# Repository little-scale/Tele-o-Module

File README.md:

# Tele-o-Module
Eurorack Module for WiFi / BlueTooth / BLE to 4 CV and 2 Gates

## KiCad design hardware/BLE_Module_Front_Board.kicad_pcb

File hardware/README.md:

Hardware files for Tele-o Module

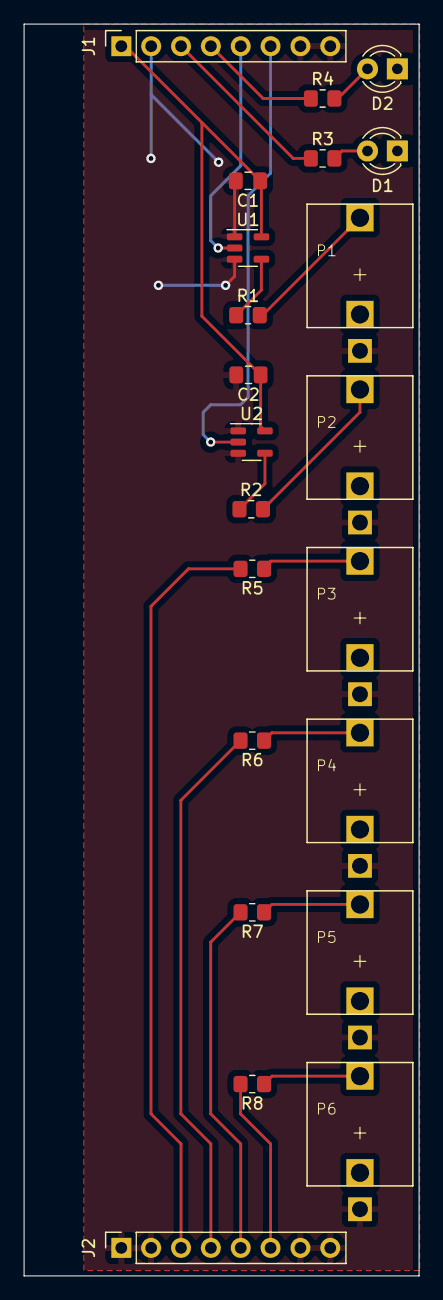
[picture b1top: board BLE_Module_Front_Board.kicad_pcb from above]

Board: 2 copper layers, 33.6 x 106.5 mm, 22 parts (0 on the bottom side), 20 nets.

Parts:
C1, C2: C; C_0805_2012Metric_Pad1.18x1.45mm_HandSolder
D1, D2: LED; LED_D3.0mm
J1, J2: Conn_01x08_Male; PinSocket_1x08_P2.54mm_Vertical
P1, P2, P3, P4, P5, P6: EuroCon; THONKICONN
R1, R2, R3, R4: 1k; R_0805_2012Metric_Pad1.20x1.40mm_HandSolder
R5, R6, R7, R8: 1K; R_0805_2012Metric_Pad1.20x1.40mm_HandSolder
U1, U2: 74AHCT1G125; SOT-23-5

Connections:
+5V: C1.1, C2.1, J1.1, U1.5 (VCC), U2.5 (VCC)
/CV1: J2.3, R5.2
/CV2: J2.4, R6.2
/CV3: J2.5, R7.2
/CV4: J2.6, R8.2
/GATE1: J1.5, U1.2
/GATE2: J1.6, U2.2
/LED1: J1.3, R3.1
/LED2: J1.4, R4.1
GND: C1.2, C2.2, D1.1 (K), D2.1 (K), J1.2, J1.7, J1.8, J2.1, J2.2, J2.7, J2.8, P1.P$1_SLEEVE, P2.P$1_SLEEVE, P3.P$1_SLEEVE, P4.P$1_SLEEVE, P5.P$1_SLEEVE, P6.P$1_SLEEVE, U1.1, U1.3 (GND), U2.1, U2.3 (GND)
unnamed: D1.2 (A), R3.2
unnamed: D2.2 (A), R4.2
unnamed: P1.P$3_TIP, R1.2
unnamed: P2.P$3_TIP, R2.2
unnamed: P3.P$3_TIP, R5.1
unnamed: P4.P$3_TIP, R6.1
unnamed: P5.P$3_TIP, R7.1
unnamed: P6.P$3_TIP, R8.1
unnamed: R1.1, U1.4
unnamed: R2.1, U2.4

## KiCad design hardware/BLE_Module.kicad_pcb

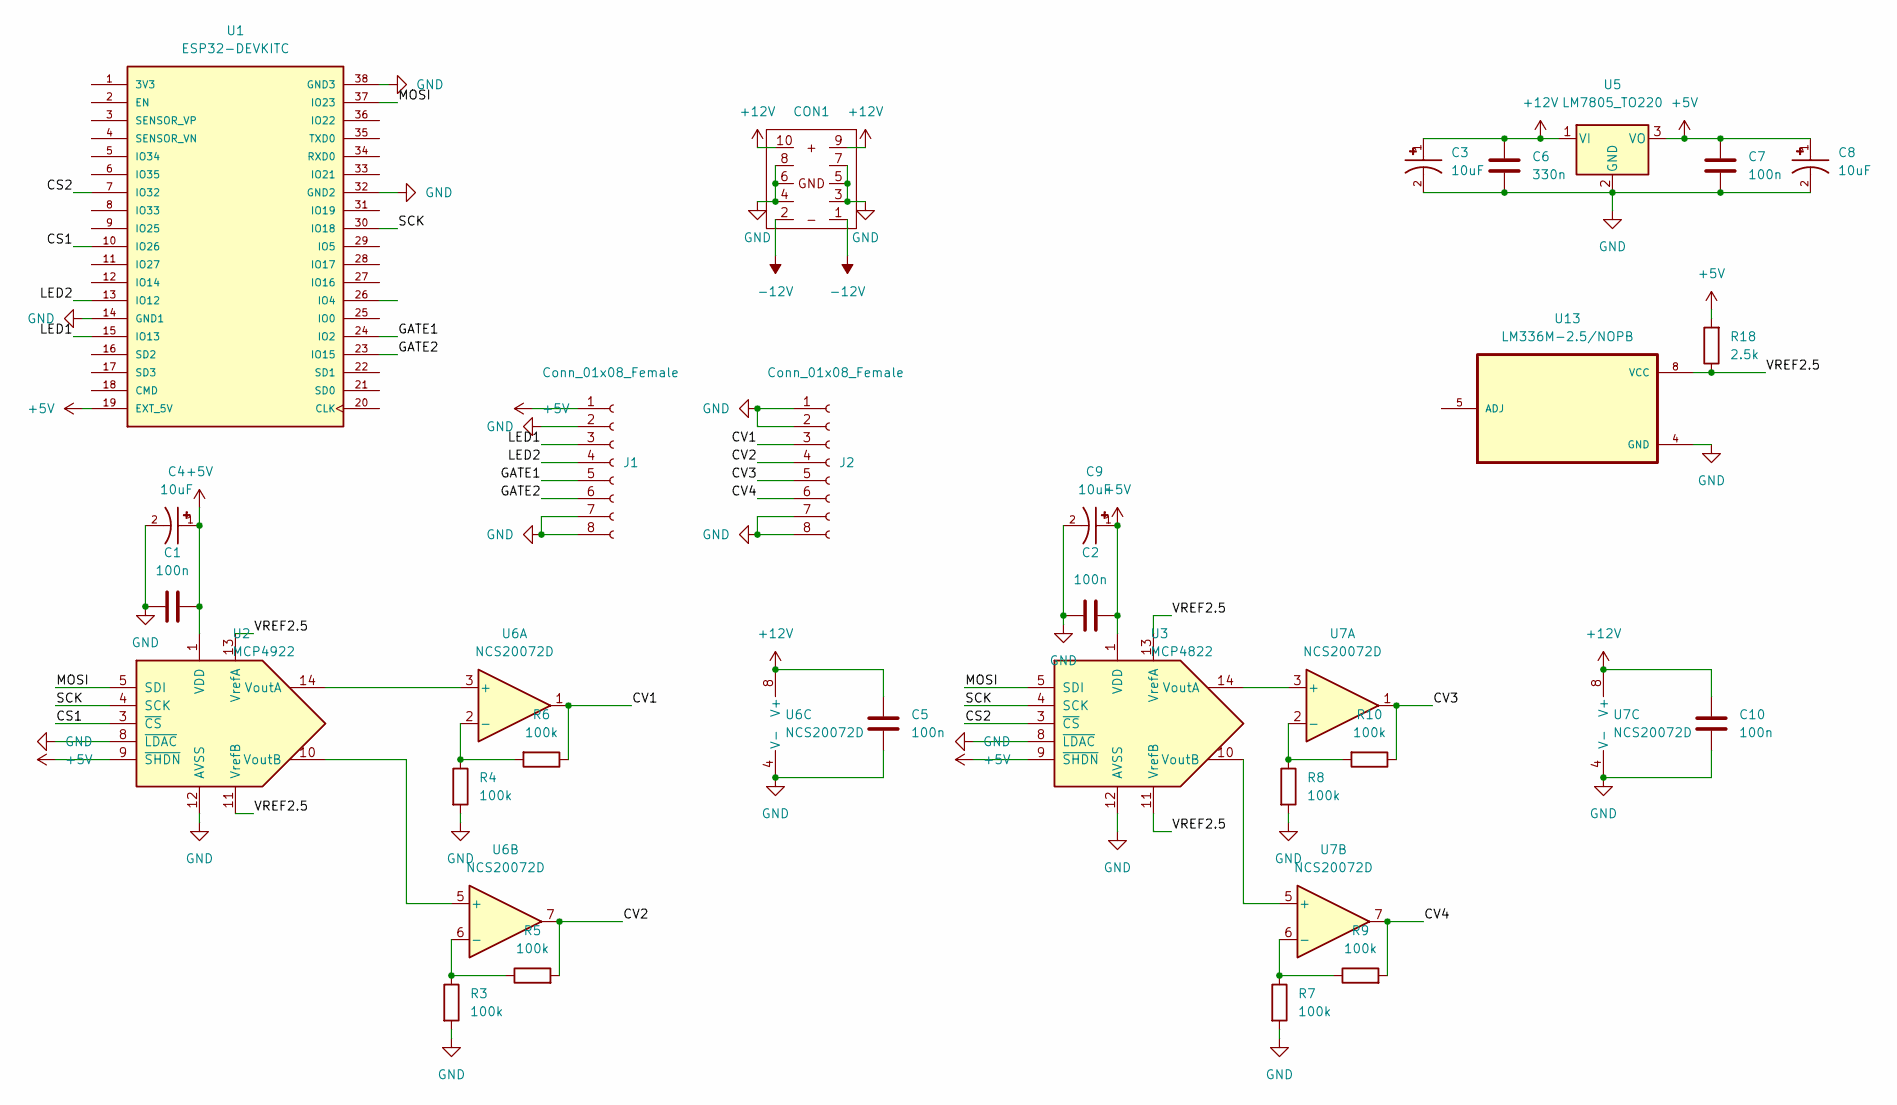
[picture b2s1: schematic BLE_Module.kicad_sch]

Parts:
C1, C2, C5, C7, C10: 100n; C_0805_2012Metric_Pad1.18x1.45mm_HandSolder
C3, C4, C8, C9: 10uF; CAP_EEEFN1E100R; PARTREV 10-Oct-19
C6: 330n; C_0805_2012Metric_Pad1.18x1.45mm_HandSolder
CON1: EuroPow; EURO_POWER_HEADER
J1, J2: Conn_01x08_Female; PinSocket_1x08_P2.54mm_Vertical
R3, R4, R5, R6, R7, R8, R9, R10: 100k; R_0805_2012Metric_Pad1.20x1.40mm_HandSolder
R18: 2.5k; R_0805_2012Metric_Pad1.20x1.40mm_HandSolder
U1: ESP32-DEVKITC; MODULE_ESP32-DEVKITC; PARTREV N/A
U2: MCP4922; SOIC127P600X175-14N
U3: MCP4822; SOIC127P600X175-14N
U5: LM7805_TO220; TO-220-3_Vertical
U6, U7: NCS20072D; SOIC-8_3.9x4.9mm_P1.27mm
U13: LM336M-2.5/NOPB; SOIC127P599X175-8N

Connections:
+5V: C1.2, C2.2, C4.1, C7.1, C8.1, C9.1, J1.1, R18.2, U1.19 (EXT_5V), U2.1 (VDD), U2.9 (~SHDN), U3.1 (VDD), U3.9 (~SHDN), U5.3 (VO)
+12V: C3.1, C5.1, C6.1, C10.1, CON1.9, CON1.10, U5.1 (VI), U6.8 (V+), U7.8 (V+)
-12V: CON1.1, CON1.2
/CS1: U1.10 (IO26), U2.3 (~CS)
/CS2: U1.7 (IO32), U3.3 (~CS)
/CV1: J2.3, R6.1, U6.1
/CV2: J2.4, R5.2, U6.7
/CV3: J2.5, R10.1, U7.1
/CV4: J2.6, R9.2, U7.7
/GATE1: J1.5, U1.24 (IO2)
/GATE2: J1.6, U1.23 (IO15)
/LED1: J1.3, U1.15 (IO13)
/LED2: J1.4, U1.13 (IO12)
/MOSI: U1.37 (IO23), U2.5 (SDI), U3.5 (SDI)
/SCK: U1.30 (IO18), U2.4 (SCK), U3.4 (SCK)
/VREF2.5: R18.1, U2.11 (VrefB), U2.13 (VrefA), U3.11 (VrefB), U3.13 (VrefA), U13.8 (VCC)
GND: C1.1, C2.1, C3.2, C4.2, C5.2, C6.2, C7.2, C8.2, C9.2, C10.2, CON1.3, CON1.4, CON1.5, CON1.6, CON1.7, CON1.8, J1.2, J1.7, J1.8, J2.1, J2.2, J2.7, J2.8, R3.2, R4.2, R7.2, R8.2, U1.14 (GND1), U1.32 (GND2), U1.38 (GND3), U2.8 (~LDAC), U2.12 (AVSS), U3.8 (~LDAC), U3.12 (AVSS), U5.2 (GND), U6.4 (V-), U7.4 (V-), U13.4 (GND)
unnamed: R3.1, R5.1, U6.6 (-)
unnamed: R4.1, R6.2, U6.2 (-)
unnamed: R7.1, R9.1, U7.6 (-)
unnamed: R8.1, R10.2, U7.2 (-)
unnamed: U2.10 (VoutB), U6.5 (+)
unnamed: U2.14 (VoutA), U6.3 (+)
unnamed: U3.10 (VoutB), U7.5 (+)
unnamed: U3.14 (VoutA), U7.3 (+)

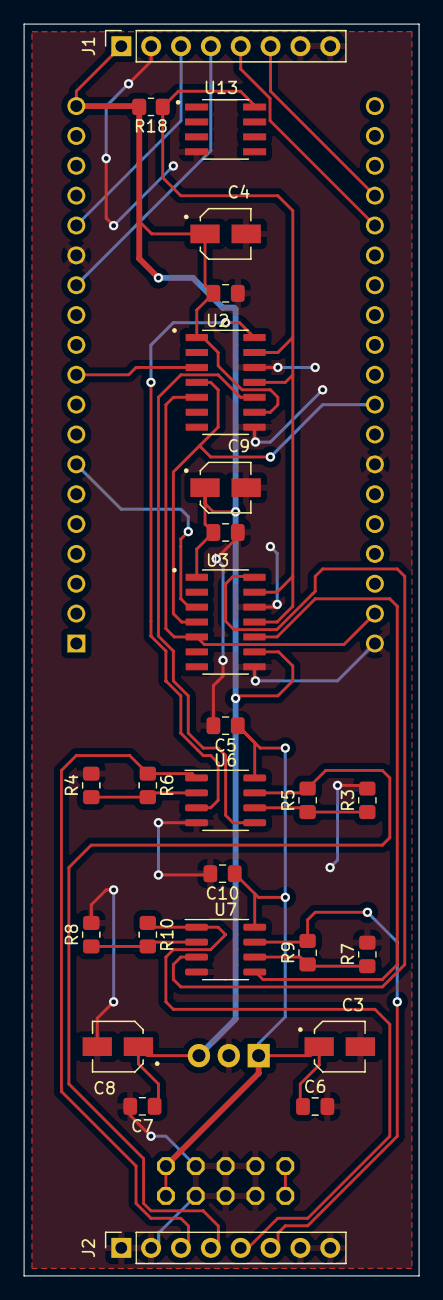
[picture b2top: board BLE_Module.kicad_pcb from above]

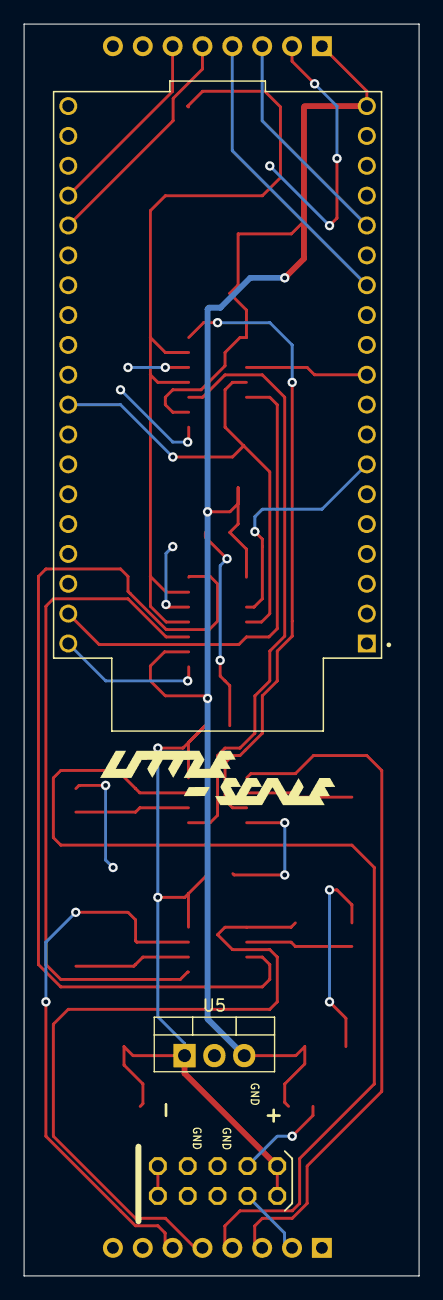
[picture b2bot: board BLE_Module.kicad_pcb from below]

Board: 2 copper layers, 33.6 x 106.5 mm, 29 parts (3 on the bottom side), 25 nets.
